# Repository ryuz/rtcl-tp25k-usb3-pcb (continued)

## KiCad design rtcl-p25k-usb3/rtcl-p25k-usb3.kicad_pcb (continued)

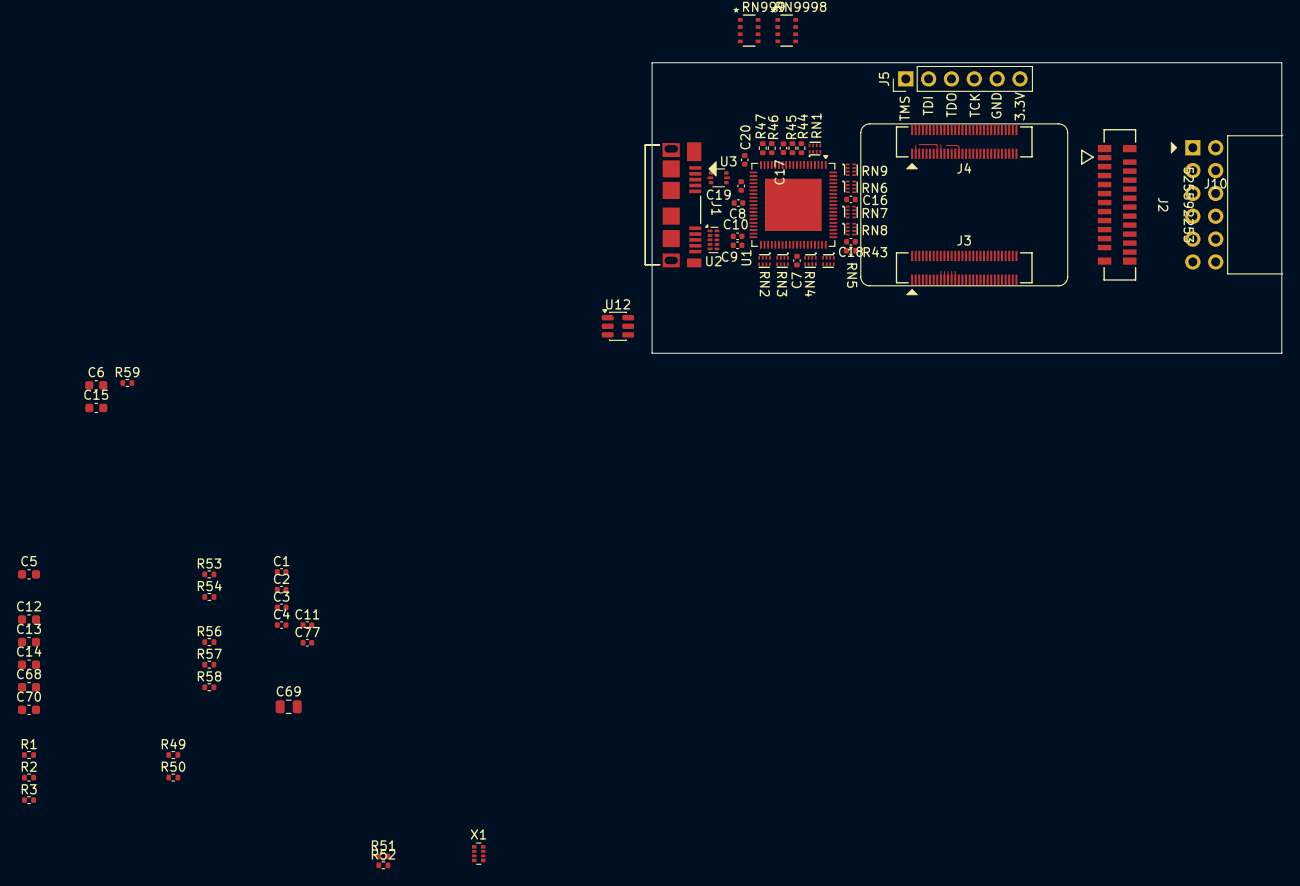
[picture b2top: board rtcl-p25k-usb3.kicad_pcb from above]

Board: 2 copper layers, 70.0 x 32.3 mm, 64 parts (0 on the bottom side), 88 nets.

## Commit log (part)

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2026-05-07 1st commit
2026-05-07 Refactor code structure for improved readability and maintainability
2026-05-08 Add new footprints for RES_YC104_YAG and RES_YC164_3P2X1P6_YAG
    - Created footprint for RES_YC104_YAG with detailed properties and pads.
    - Created footprint for RES_YC164_3P2X1P6_YAG with comprehensive design elements and specifications.
2026-05-08 Add FT601Q symbol to KiCad library
    - Created a new symbol for the FT601Q USB 3.0 FIFO interface IC.
    - Included properties such as Reference, Value, Footprint, Datasheet, and Description.
    - Defined 77 pins with appropriate names, types, and attributes.
    - Ensured compatibility with KiCad version 10.0 and included necessary font settings.
2026-05-08 Update KiCad project files for rtcl-p25k-usb3
    - Changed active layer from 25 to 5 in the project file.
    - Updated footprint property for components in the schematic:
    - Changed footprint for a connector to "rtcl-p25k-usb3:CON_525592253_MOL".
    - Updated value for a component from "BTB-DF40C-60DS-0.4V(51)" to "DF40C-60DS-0.4V(51)".
    - Changed footprint for another component to "rtcl-p25k-usb3:PMOD_02x06_2.54mm".
    - Modified UUIDs for various graphical elements in the CONN_DF40C-60DS_HIR module.
2026-05-09 rename
2026-05-09 Update model paths in KiCad module files for consistency
    - Changed model path for CONN10_ZX360D-B-10P30_HIR.kicad_mod to reflect the correct directory structure.
    - Updated model path for CONN_DF40C-60DS_HIR.kicad_mod to point to the new location.
    - Modified model path for CON_525592253_MOL.kicad_mod to ensure it aligns with the updated project directory.
2026-05-09 コネクタ反転判明
2026-05-10 Update project settings and parameters
    - Modified selection filter settings in the .kicad_prl file to disable footprint and locked items selection.
    - Added a new parameter value (0.12954) to the list in the .kicad_pro file for improved configuration.
2026-05-10 Add PCB statistics report for rtcl-tp25k-usb3 project
    - Include detailed dimensions, area, and component density
    - Document pad and via counts
    - Provide drill hole specifications
2026-05-10 Add normalized length table and update pin assignment files
2026-05-10 Update KiCad project files and add pin assignment documentation
    - Changed selection filter for footprints in the KiCad project rules file to true.
    - Adjusted minimum clearance value in the KiCad project settings from 0.5 to 0.2.
    - Added new Excel file for pin assignments with lengths to the documentation directory.
2026-05-10 Update KiCad project files and component definitions
    - Changed active layer from 4 to 0 in the project settings.
    - Enabled text visibility in the board settings.
    - Adjusted clearance values for various classes in the project configuration to improve design rules.
    - Updated UUIDs for multiple elements in the component definition file to ensure uniqueness and avoid conflicts.
    - Removed redundant lines in the component definition for clarity and conciseness.
2026-05-10 Update .gitignore and modify active layer in KiCad project file
2026-05-10 Refactor PCB and schematic files for improved layout and component management
    - Updated active layer in the PCB design from 31 to 25 for better visibility.
    - Disabled text display in the PCB design to reduce clutter.
    - Removed unnecessary junctions and wires from the schematic to streamline the design.
    - Adjusted component placements and properties, including resistors and capacitors, for better alignment and readability.
    - Changed UUIDs for various elements in the schematic and PCB files to ensure uniqueness and prevent conflicts.
    - Updated the connector module with new UUIDs and cleaned up unnecessary geometry.
2026-05-11 Refactor KiCad project files for improved layout and organization
    - Updated active layer in the project file to layer 5 for better visibility.
    - Modified selection filter settings to hide dimensions, footprints, graphics, keepouts, other items, pads, tracks, vias, and zones.
    - Cleared used designators in the project file to streamline component management.
    - Adjusted junction and wire coordinates in the schematic for better alignment and clarity.
    - Renamed labels in the schematic for consistency and clarity.
    - Updated component positions and properties in the schematic to enhance layout.
2026-05-11 Update footprint and text attributes in KiCad project files for improved clarity and accuracy
2026-05-14 Refactor KiCad project files: update active layer, toggle visibility settings, and remove unnecessary junctions and wires
    - Changed active layer from 5 to 0 in the .kicad_prl file.
    - Modified visibility settings for text, tracks, and vias in the .kicad_prl file.
    - Updated visible layers string in the .kicad_prl file.
    - Removed redundant junctions and wires from the .kicad_sch file to clean up the schematic.
    - Added new wire connections and labels for better clarity in the .kicad_sch file.
    - Adjusted positions of several labels for improved layout in the .kicad_sch file.
2026-05-14 Update active layer in PCB design to layer 6
2026-05-14 Update active layer and selection filter settings in KiCad project file
    - Changed active_layer from 6 to 0 for initial layer setup.
    - Disabled footprint selection in the filter.
    - Enabled locked items in the selection filter.
    - Disabled via selection in the filter.
2026-05-14 Update selection filter settings in KiCad project file
    - Changed selection filter options to enable visibility for dimensions, footprints, graphics, keepouts, locked items, other items, pads, text, vias, and zones.
    - This enhances the usability of the design environment by allowing more elements to be selected and manipulated.
2026-05-14 DRCは通した
2026-05-14 PMOD配線長調整
2026-05-14 Update KiCad project settings and add length table for Tang Primer 25K
    - Changed active layer from 2 to 4 in the KiCad project file.
    - Updated selection filter to enable visibility for dimensions, footprints, graphics, keepouts, other items, pads, text, vias, and zones.
    - Modified visible layers and zone display mode in the KiCad project file.
    - Added a new Excel file for the Tang Primer 25K length table in the documentation directory.
2026-05-16 Update visible_layers in rtcl-tp25k-usb3.kicad_prl to correct layer visibility settings
2026-05-16 Fix visibility settings in KiCad project file for improved layer management
2026-05-16 Update active layer and visible layers in KiCad project file
    - Changed active layer from 0 to 4 for improved design visibility.
    - Updated visible layers from "00000000_00000000_00000080_82082027" to "00000000_00000000_00000080_82082077" to reflect new layer settings.
    - Modified zone display mode from 1 to 0 for better layout management.
2026-05-21 Update KiCad project settings: change active layer to 0, adjust selection filter and visible layers
2026-05-21 Add RASPPICAM22_REV symbol and AFC11-S22ICA-00 footprint
    - Introduced a new symbol "RASPPICAM22_REV" with properties including Reference, Value, Footprint, and LCSC.
    - Added detailed pin definitions for the RASPPICAM22_REV symbol, including power, input, and output pins.
    - Created a new footprint "AFC11-S22ICA-00" with defined pads and properties, including reference and value text.
    - Included model path for the footprint to facilitate 3D visualization.
2026-05-21 Update KiCad project files: change active layer and modify selection filter settings
    - Changed active layer from 0 to 25 in the .kicad_prl file.
    - Updated selection filter settings to disable visibility for dimensions, footprints, graphics, keepouts, pads, text, tracks, and vias, while keeping locked items and zones visible.
    - Modified visible layers string in the .kicad_prl file.
    - Added a new property "LCSC" with value "C6332199" for a component in the .kicad_sch file.
    - Updated the "LCSC" property value from "C37208" to "C2897426" for another component in the .kicad_sch file.
2026-05-21 Update BOM: correct part numbers for J10 and J5
2026-05-21 Update PCB and schematic files with new component properties and adjustments
    - Added LCSC properties for components C4364316, C15402, and C40059 in the PCB and schematic files.
    - Adjusted reference positions for capacitors C24 and C7, and resistors R60 and R61 for better alignment.
    - Updated the value property for components from "AFC11-S22ICA-00" to "MIPI_22pin" and "SSQ-106-02-F-D-RA" to "PMOD".
    - Modified selection filter settings in the PCB layout to enable graphics and text visibility while disabling locked items and zones.
    - Adjusted graphical elements in the PCB layout for improved clarity and alignment.
2026-05-22 Implement feature X to enhance user experience and fix bug Y in module Z
2026-05-22 発注時にWebで直した部分など修正
2026-05-23 YC124-FR-0722RL に変更
2026-05-23 Update BOM and schematic files with new LCSC properties and component adjustments
2026-05-24 Update active layer and text visibility in KiCad project settings
    - Changed active layer from 0 to 5 for improved design focus.
    - Enabled text visibility for better readability in the layout.
    - Adjusted zone display mode from 1 to 0 for a different rendering approach
2026-05-25 Update footprint properties to RES_YC124_4x1_JLCPCB and add new footprint file
2026-05-25 Update active layer and visibility settings in KiCad project file
    - Changed active layer from 5 to 0 for improved layout management.
    - Updated visibility settings to hide text and show tracks, enhancing design clarity.
2026-05-25 Refactor polygon coordinates in PCB layout for improved accuracy and readability
    - Adjusted multiple coordinate points in the rtcl-tp25k-usb3.kicad_pcb file to enhance the precision of the layout.
    - Updated specific segments of filled polygons to ensure better alignment and representation of the design.
    - Cleaned up redundant points and optimized the overall structure of the coordinate definitions.
2026-05-26 Update PCB design and component footprint for rtcl-tp25k-usb3
    - Enabled vias in the PCB layout for better connectivity.
    - Adjusted visible layers for improved design visibility.
    - Modified UUIDs for various graphical elements in the SOT_34NT1G_ONS footprint.
    - Updated pad dimensions and positions for better alignment with the component specifications.
2026-05-29 Update selection filter settings in KiCad project for improved visibility
2026-06-28 SW3を回転させシルクを修正
2026-06-29 Add English and Japanese README files for Tang Primer 25K base board project
2026-06-29 ダンピング抵抗除去
